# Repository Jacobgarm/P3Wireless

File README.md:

# P3Wireless

Christian, Emil og Jacob

Kode til både server og client i vores P3 projekt om trådløs kommunikation. Serveren skal fremvise data, mens clienten skal opsamle og sende data. Kommunnikation foregår over BLE.

Features:
Målestation / Server
- Bluetooth low energy
- Temperatur- og luftfugtighedsmåler

Hjemmebase / Client
- Bluetooth low energy
- DAC til lyd
- LCD
- Knapper til input
- SD-kort til logging

ClientFinal og ServerFinal indeholder de versioner af koden der bruges i det endelige produkt.

EagleSketches indeholder de elektriske diagrammer ogver stationerne.

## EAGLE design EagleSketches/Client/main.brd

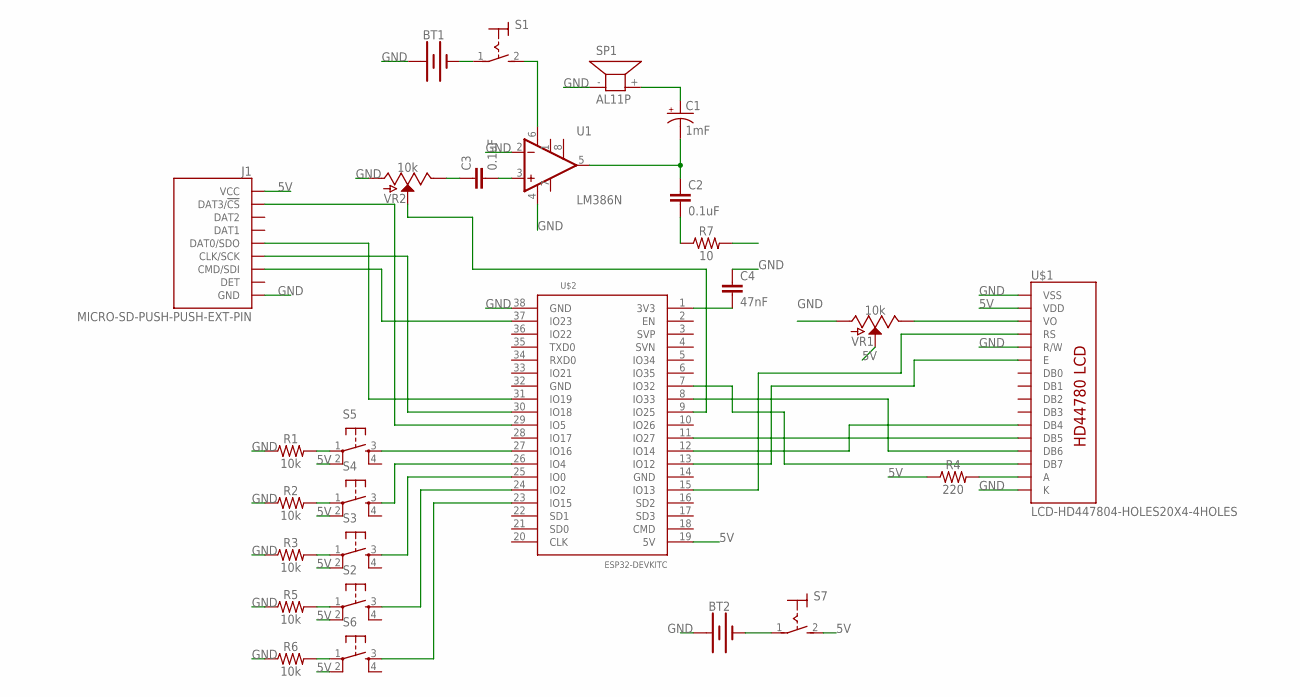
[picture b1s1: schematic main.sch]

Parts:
BT1, BT2: BATTERY-9V; BATTCON_9V
C1: 1mF; CPOL-RADIAL-5MM-10MM
C2, C3: 0.1uF; CAP-PTH-SMALL-KIT
C4: 47nF; 0603
J1: MICRO-SD-PUSH-PUSH-EXT-PIN; MICROSD-EXTERNALPIN
R1, R2, R3, R5, R6: 10k; AXIAL-0.3
R4: 220; 0603
R7: 10; AXIAL-0.3
S1, S7: MS243
S2, S3, S4, S5, S6: TAC_SWITCHPTH; TACTILE-PTH
SP1: AL11P
U1: LM386N; DIP08
U$1: LCD-HD447804-HOLES20X4-4HOLES; LCD-20X4-4HOLES
U$2: ESP32DEVKITC; ESP32-DEVKITC
VR1, VR2: 10k; SLIDER-XLARGE

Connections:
5V: J1.4 (VCC), R4.1, S2.2, S3.2, S4.2, S5.2, S6.2, S7.2 (S), U$1.P$2 (VDD), U$2.19 (5V), VR1.2A (S)
GND: BT1.+, BT2.+, C4.1, J1.6 (GND), J1.10 (GND), J1.11 (GND), J1.12 (GND), J1.13 (GND), R1.P$1 (1), R2.P$1 (1), R3.P$1 (1), R5.P$1 (1), R6.P$1 (1), SP1.- (1), U1.2 (-IN), U1.4 (V-), U$1.P$1 (VSS), U$1.P$5 (R/W), U$1.P$16 (K), U$2.38 (GND), VR1.3 (A), VR2.3 (A)
unnamed: U$1.P$3 (VO), VR1.1 (E)
unnamed: U$1.P$4 (RS), U$2.15 (IO13)
unnamed: U$1.P$6 (E), U$2.13 (IO12)
unnamed: R4.2, U$1.P$15 (A)
unnamed: S2.3, U$2.24 (IO2)
unnamed: U$1.P$13 (DB6), U$2.8 (IO33)
unnamed: U$1.P$11 (DB4), U$2.12 (IO14)
unnamed: U$1.P$12 (DB5), U$2.11 (IO27)
unnamed: S6.3, U$2.23 (IO15)
unnamed: R6.P$2 (2), S6.1
unnamed: C1.+, SP1.+ (2)
unnamed: R5.P$2 (2), S2.1
unnamed: C1.-, C2.1, U1.5 (OUT)
unnamed: R3.P$2 (2), S3.1
unnamed: U$1.P$14 (DB7), U$2.7 (IO32)
unnamed: S3.3, U$2.25 (IO0)
unnamed: S4.3, U$2.26 (IO4)
unnamed: S5.3, U$2.27 (IO16)
unnamed: C2.2, R7.P$1 (1)
unnamed: U$2.9 (IO25), VR2.2A (S)
unnamed: BT1.-, S1.1
unnamed: C3.1, VR2.1 (E)
unnamed: R2.P$2 (2), S4.1
unnamed: J1.2 (DAT3/!CS!), U$2.29 (IO5)
unnamed: R1.P$2 (2), S5.1
unnamed: J1.5 (CLK/SCK), U$2.30 (IO18)
unnamed: J1.3 (CMD/SDI), U$2.37 (IO23)
unnamed: J1.7 (DAT0/SDO), U$2.31 (IO19)
unnamed: C3.2, U1.3 (+IN)
unnamed: S1.2 (S), U1.6 (V+)
unnamed: C4.2, U$2.1 (3V3)
unnamed: BT2.-, S7.1

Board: 2 copper layers, 27 parts (0 on the bottom side), 34 nets, no tracks yet.

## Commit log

2021-12-13 Nye filer for at teste kompoenter
2021-12-13 rfe76wqef8terf
2021-12-15 Tilføjet ny client baseret på eksempel
2022-01-04 Eagle sketch tilføjet
    Client
2022-01-07 idk
    sever klient
2022-01-10 Ealge server
    sejt
2022-01-10 Nye UUID's og eagle ændringer
2022-01-10 Tilgøjet diverse funktioner til softwaren
    Logging, muting, buttons, display, sensorer
2022-01-11 Tidsplan
    hej
2022-01-12 Logging system
2022-01-18 Client kode + eagle
    Logging, LCD states og Eagle sketch med SD
2022-01-23 Alarm part 1
2022-01-24 Final pins + mere
2022-02-01 Working audio
2022-02-04 eglage
    Elage
2022-02-04 Endelige versioner af koden
2022-02-04 Skiftet filnavne mm
2022-02-04 Degree symbol
2022-02-06 Update readme + cleanup
2022-02-07 Eagle fix

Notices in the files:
parts and their libraries:
SparkFun-Resistors: Licensing: Creative Commons ShareAlike 4.0 International - https://creativecommons.org/licenses/by-sa/4.0
